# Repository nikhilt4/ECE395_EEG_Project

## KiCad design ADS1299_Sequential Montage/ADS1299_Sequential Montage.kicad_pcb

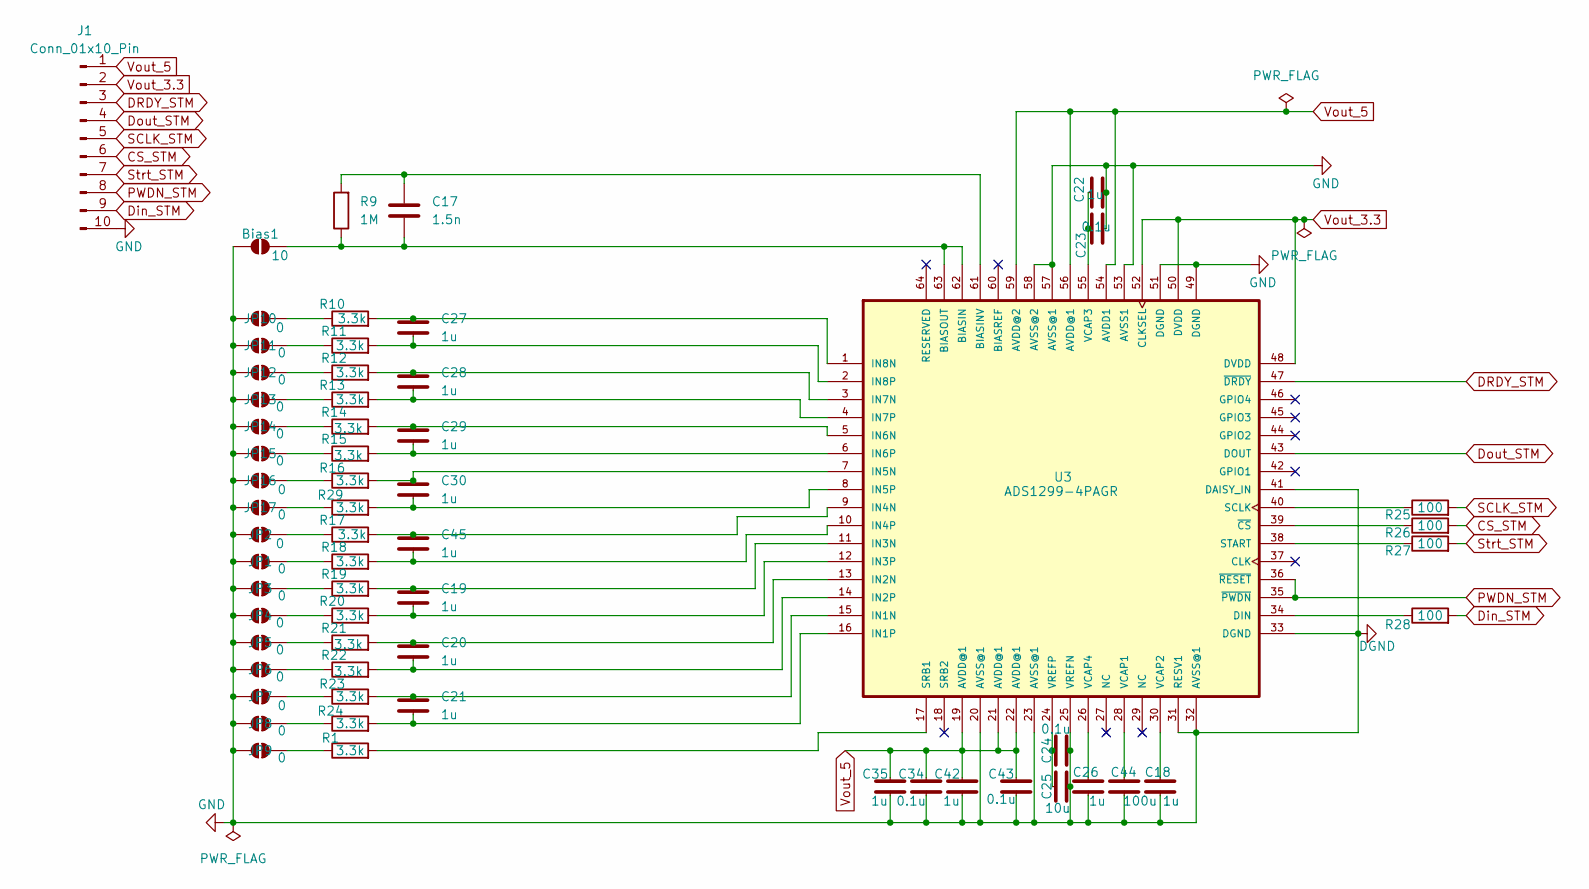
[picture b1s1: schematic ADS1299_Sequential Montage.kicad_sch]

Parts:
Bias1: 10; PinHeader_1x02_P2.54mm_Vertical
C17: 1.5n; C_0805_2012Metric_Pad1.18x1.45mm_HandSolder
C18, C19, C20, C21, C22, C26, C27, C28, C29, C30, C35, C42, C45: 1u; C_0805_2012Metric_Pad1.18x1.45mm_HandSolder
C23, C24, C34, C43: 0.1u; C_0805_2012Metric_Pad1.18x1.45mm_HandSolder
C25: 10u; C_0805_2012Metric_Pad1.18x1.45mm_HandSolder
C44: 100u; C_0805_2012Metric_Pad1.18x1.45mm_HandSolder
J1: Conn_01x10_Pin; PinHeader_1x10_P2.54mm_Vertical
JP1, JP2, JP3, JP4, JP5, JP6, JP7, JP8, JP9, JP10, JP11, JP12, JP13, JP14, JP15, JP16, JP17: 0; PinHeader_1x02_P2.54mm_Vertical
R1, R10, R11, R12, R13, R14, R15, R16, R17, R18, R19, R20, R21, R22, R23, R24, R29: 3.3k; R_0805_2012Metric_Pad1.20x1.40mm_HandSolder
R9: 1M; R_0805_2012Metric_Pad1.20x1.40mm_HandSolder
R25, R26, R27, R28: 100; R_0805_2012Metric_Pad1.20x1.40mm_HandSolder
U3: ADS1299-4PAGR; QFP50P1200X1200X120-64N

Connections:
CS_STM: J1.6, R26.2
DGND: Bias1.1 (A), C18.2, C22.2, C23.2, C24.2, C25.2, C26.2, C34.2, C35.2, C42.2, C43.2, C44.2, J1.10, JP1.1 (A), JP2.1 (A), JP3.1 (A), JP4.1 (A), JP5.1 (A), JP6.1 (A), JP7.1 (A), JP8.1 (A), JP9.1 (A), JP10.1 (A), JP11.1 (A), JP12.1 (A), JP13.1 (A), JP14.1 (A), JP15.1 (A), JP16.1 (A), JP17.1 (A), U3.20 (AVSS@1), U3.23 (AVSS@1), U3.25 (VREFN), U3.31 (RESV1), U3.32 (AVSS@1), U3.33 (DGND), U3.41 (DAISY_IN), U3.49 (DGND), U3.51 (DGND), U3.53 (AVSS1), U3.57 (AVSS@1), U3.58 (AVSS@2)
DRDY_STM: J1.3, U3.47 (~DRDY)
Din_STM: J1.9, R28.2
Dout_STM: J1.4, U3.43 (DOUT)
unnamed: Bias1.2 (B), C17.1, R9.1, U3.62 (BIASIN), U3.63 (BIASOUT)
unnamed: JP1.2 (B), R18.1
unnamed: JP2.2 (B), R17.1
unnamed: JP3.2 (B), R19.1
unnamed: JP4.2 (B), R20.1
unnamed: JP5.2 (B), R21.1
unnamed: JP6.2 (B), R22.1
unnamed: JP7.2 (B), R23.1
unnamed: JP8.2 (B), R24.1
unnamed: JP9.2 (B), R1.1
unnamed: JP10.2 (B), R10.1
unnamed: JP11.2 (B), R11.1
unnamed: JP12.2 (B), R12.1
unnamed: JP13.2 (B), R13.1
unnamed: JP14.2 (B), R14.1
unnamed: JP15.2 (B), R15.1
unnamed: JP16.2 (B), R16.1
unnamed: JP17.2 (B), R29.1
unnamed: C17.2, R9.2, U3.61 (BIASINV)
unnamed: R28.1, U3.34 (DIN)
unnamed: C21.1, R23.2, U3.15 (IN1N)
unnamed: C21.2, R24.2, U3.16 (IN1P)
unnamed: C20.1, R21.2, U3.13 (IN2N)
unnamed: C20.2, R22.2, U3.14 (IN2P)
unnamed: C19.1, R19.2, U3.11 (IN3N)
unnamed: C19.2, R20.2, U3.12 (IN3P)
unnamed: C45.1, R17.2, U3.9 (IN4N)
unnamed: C45.2, R18.2, U3.10 (IN4P)
unnamed: C30.1, R16.2, U3.7 (IN5N)
unnamed: C30.2, R29.2, U3.8 (IN5P)
unnamed: C29.1, R14.2, U3.5 (IN6N)
unnamed: C29.2, R15.2, U3.6 (IN6P)
unnamed: C28.1, R12.2, U3.3 (IN7N)
unnamed: C28.2, R13.2, U3.4 (IN7P)
unnamed: C27.1, R10.2, U3.1 (IN8N)
unnamed: C27.2, R11.2, U3.2 (IN8P)
unnamed: R25.1, U3.40 (SCLK)
unnamed: R1.2, U3.17 (SRB1)
unnamed: R27.1, U3.38 (START)
unnamed: C44.1, U3.28 (VCAP1)
unnamed: C18.1, U3.30 (VCAP2)
unnamed: C22.1, C23.1, U3.55 (VCAP3)
unnamed: C26.1, U3.26 (VCAP4)
unnamed: C24.1, C25.1, U3.24 (VREFP)
unnamed: R26.1, U3.39 (~CS)
PWDN_STM: J1.8, U3.35 (~PWDN), U3.36 (~RESET)
SCLK_STM: J1.5, R25.2
Strt_STM: J1.7, R27.2
Vout_3.3: J1.2, U3.48 (DVDD), U3.50 (DVDD), U3.52 (CLKSEL)
Vout_5: C34.1, C35.1, C42.1, C43.1, J1.1, U3.19 (AVDD@1), U3.21 (AVDD@1), U3.22 (AVDD@1), U3.54 (AVDD1), U3.56 (AVDD@1), U3.59 (AVDD@2)

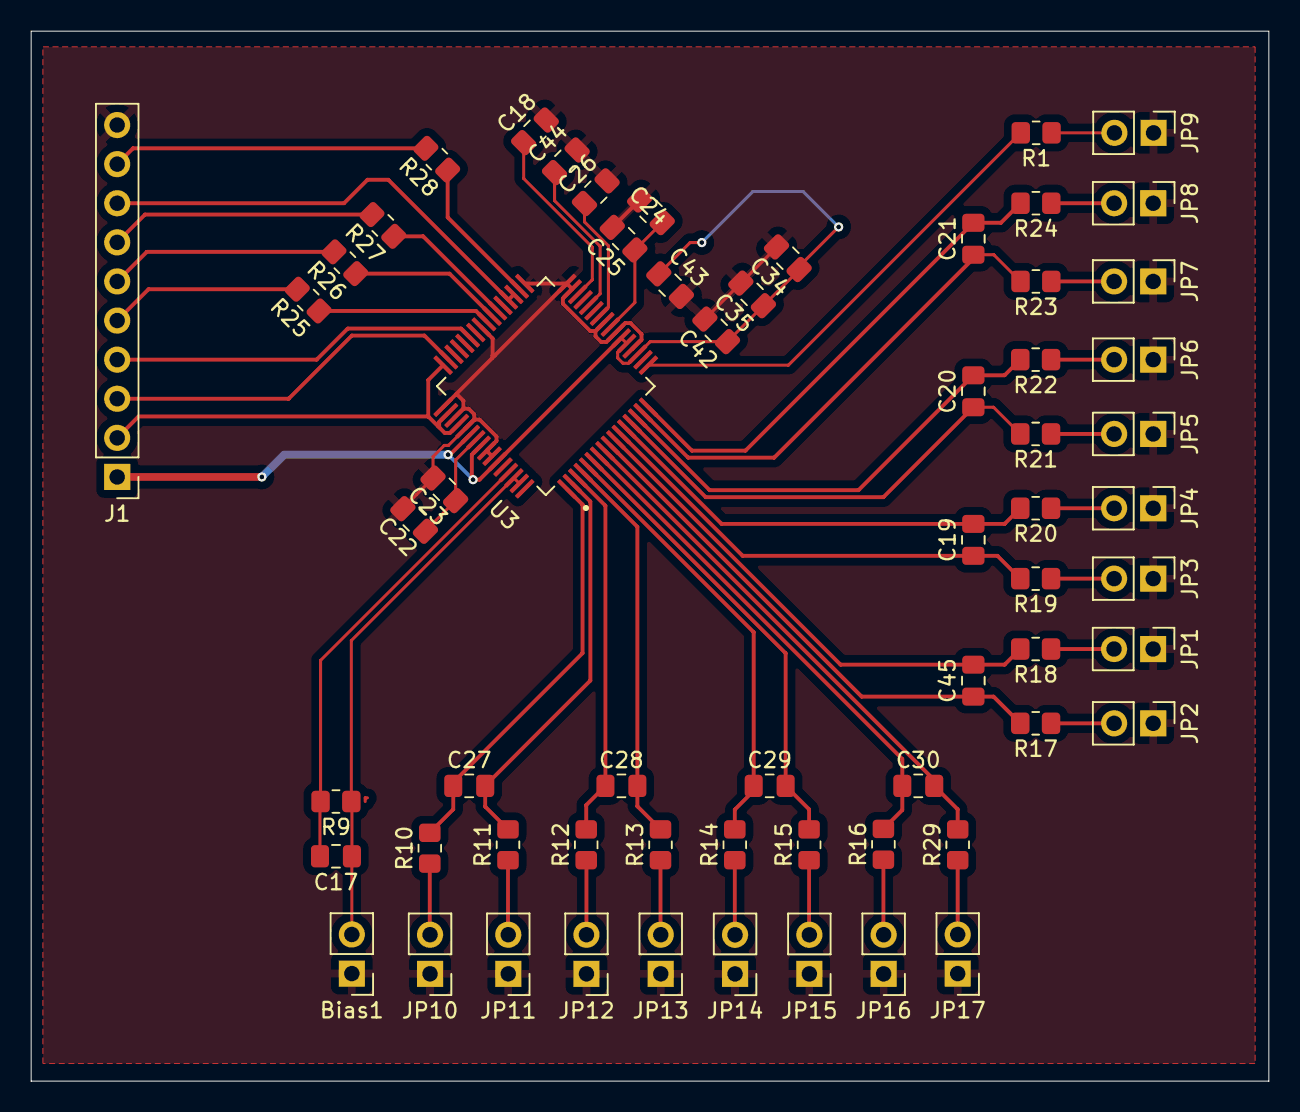
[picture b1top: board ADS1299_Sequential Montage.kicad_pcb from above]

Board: 2 copper layers, 80.4 x 68.2 mm, 62 parts (0 on the bottom side), 55 nets.

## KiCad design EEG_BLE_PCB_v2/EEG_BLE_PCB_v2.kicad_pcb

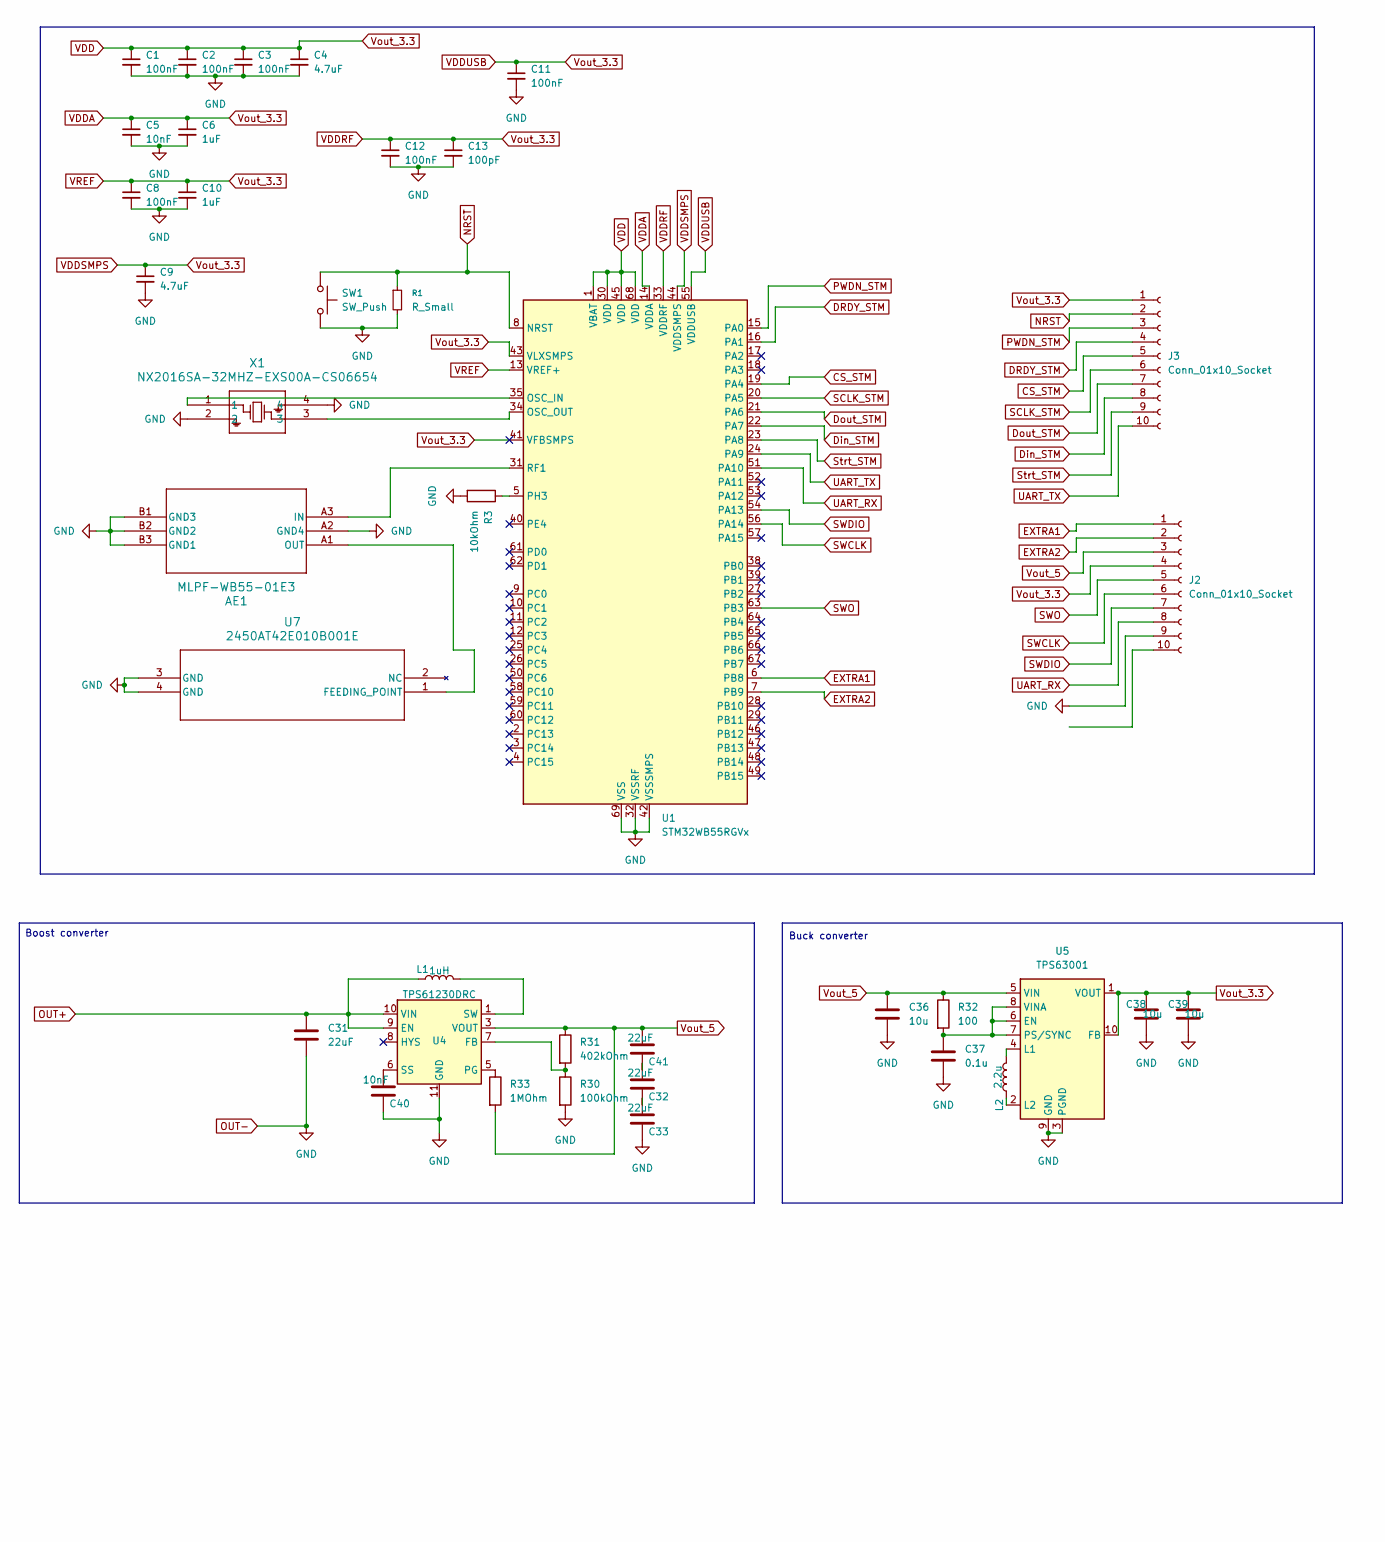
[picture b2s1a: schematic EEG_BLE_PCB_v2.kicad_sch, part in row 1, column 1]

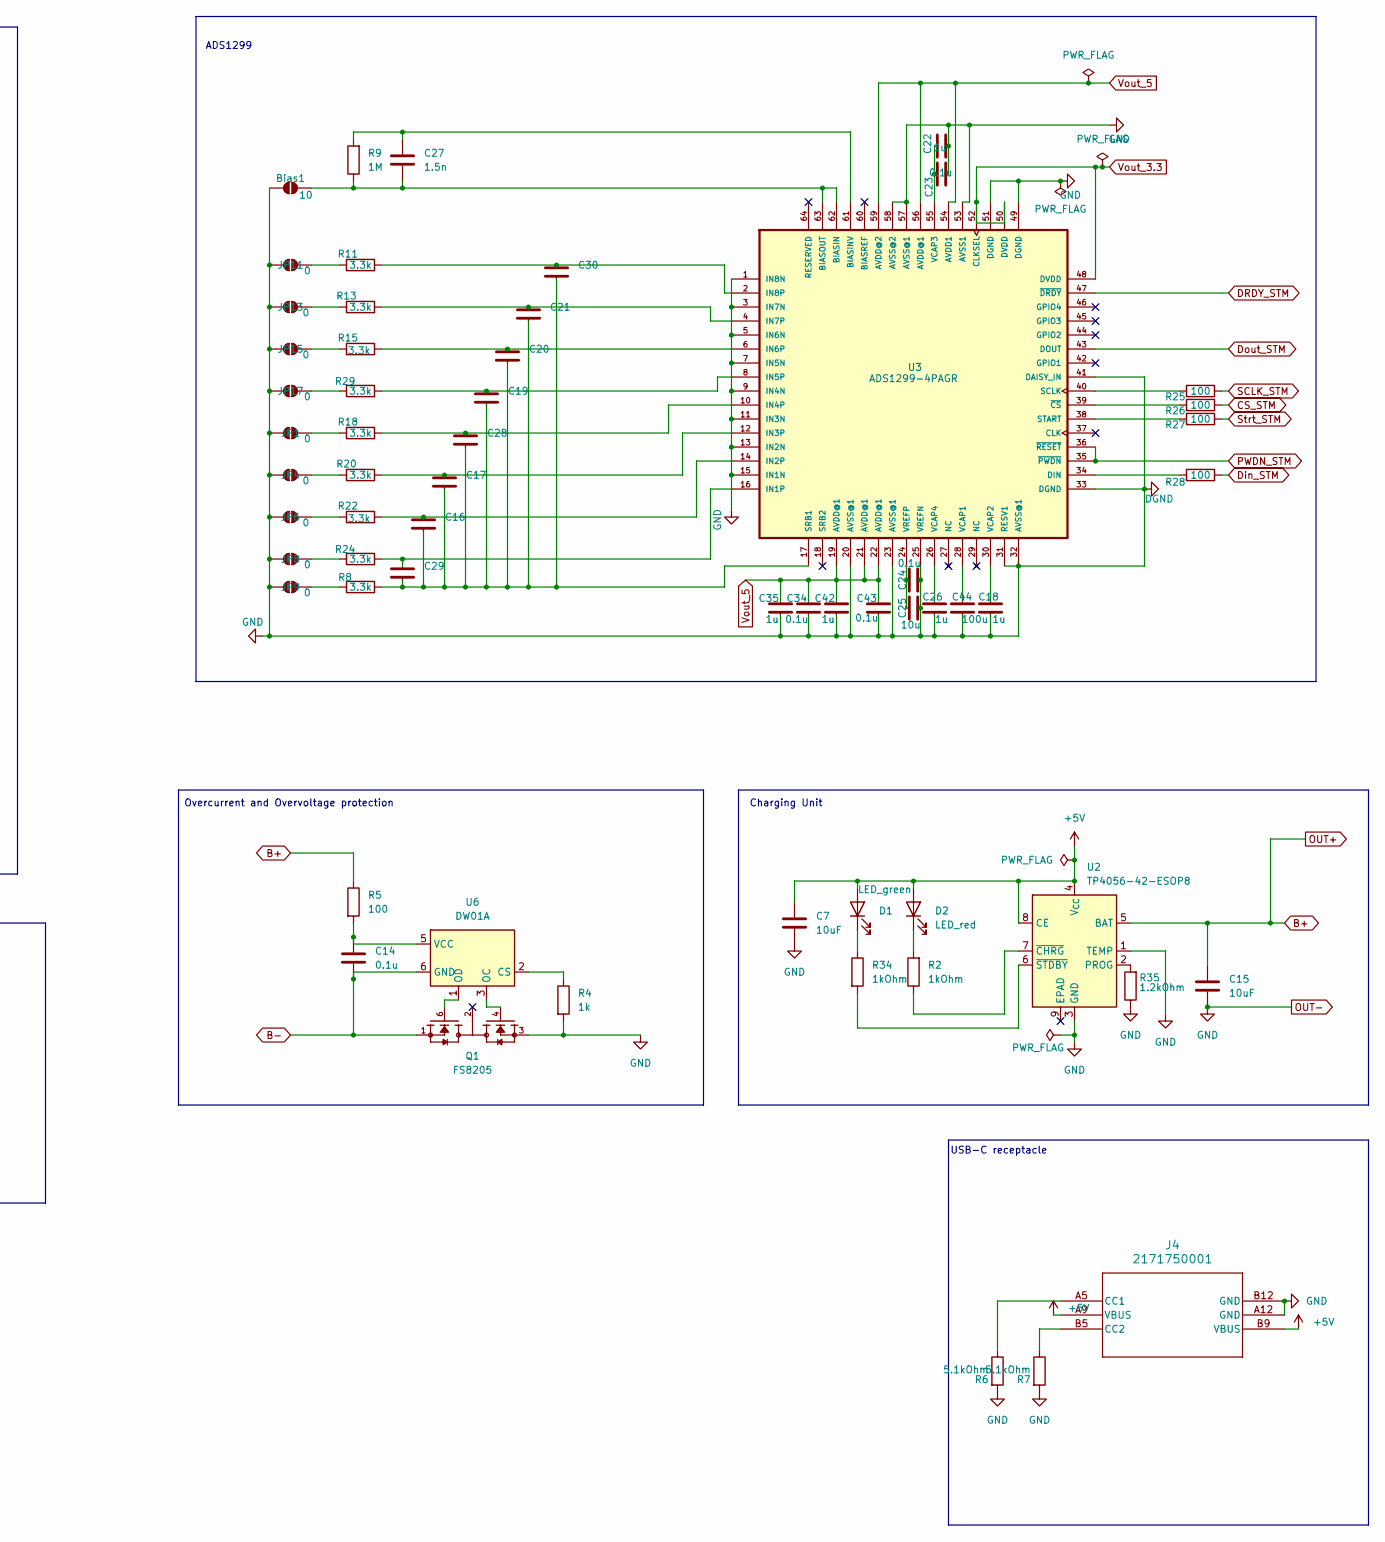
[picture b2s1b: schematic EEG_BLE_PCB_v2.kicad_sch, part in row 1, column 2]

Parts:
AE1: MLPF-WB55-01E3; MLPF-WB55-01E3_STM
Bias1: 10; PinHeader_1x02_P2.54mm_Vertical
C1, C2, C3, C8, C11, C12: 100nF; C_0805_2012Metric_Pad1.18x1.45mm_HandSolder
C4, C9: 4.7uF; C_0805_2012Metric_Pad1.18x1.45mm_HandSolder
C5, C40: 10nF; C_0805_2012Metric_Pad1.18x1.45mm_HandSolder
C6, C10: 1uF; C_0805_2012Metric_Pad1.18x1.45mm_HandSolder
C7, C15: 10uF; C_0805_2012Metric_Pad1.18x1.45mm_HandSolder
C13: 100pF; C_0805_2012Metric_Pad1.18x1.45mm_HandSolder
C14, C23, C24, C34, C37, C43: 0.1u; C_0805_2012Metric_Pad1.18x1.45mm_HandSolder
C16, C17, C19, C20, C21, C28, C29, C30: 100n; C_0805_2012Metric_Pad1.18x1.45mm_HandSolder
C18, C22, C26, C35, C42: 1u; C_0805_2012Metric_Pad1.18x1.45mm_HandSolder
C25, C36, C38, C39: 10u; C_0805_2012Metric_Pad1.18x1.45mm_HandSolder
C27: 1.5n; C_0805_2012Metric_Pad1.18x1.45mm_HandSolder
C31, C32, C33, C41: 22uF; C_0805_2012Metric_Pad1.18x1.45mm_HandSolder
C44: 100u; C_0805_2012Metric_Pad1.18x1.45mm_HandSolder
D1: LED_green; LED_0805_2012Metric_Pad1.15x1.40mm_HandSolder
D2: LED_red; LED_0805_2012Metric_Pad1.15x1.40mm_HandSolder
J2, J3: Conn_01x10_Socket; PinSocket_1x10_P2.54mm_Vertical
J4: 2171750001; 2171750001_MOL
JP1, JP4, JP6, JP8, JP9, JP11, JP13, JP15, JP17: 0; PinHeader_1x02_P2.54mm_Vertical
L1: 1uH; IND_IHLP-1616AB_VIS
L2: 2.2u; IND_VLS3012HBX-2R2M
Q1: FS8205; SOT95P280X145-6N; PARTREV 1.9
R1: R_Small; R_0805_2012Metric_Pad1.20x1.40mm_HandSolder
R2, R34: 1kOhm; R_0805_2012Metric_Pad1.20x1.40mm_HandSolder
R3: 10kOhm; R_0805_2012Metric_Pad1.20x1.40mm_HandSolder
R4: 1k; R_0805_2012Metric_Pad1.20x1.40mm_HandSolder
R5, R25, R26, R27, R28, R32: 100; R_0805_2012Metric_Pad1.20x1.40mm_HandSolder
R6, R7: 5.1kOhm; R_0805_2012Metric_Pad1.20x1.40mm_HandSolder
R8, R11, R13, R15, R18, R20, R22, R24, R29: 3.3k; R_0805_2012Metric_Pad1.20x1.40mm_HandSolder
R9: 1M; R_0805_2012Metric_Pad1.20x1.40mm_HandSolder
R30: 100kOhm; R_0805_2012Metric_Pad1.20x1.40mm_HandSolder
R31: 402kOhm; R_0805_2012Metric_Pad1.20x1.40mm_HandSolder
R33: 1MOhm; R_0805_2012Metric_Pad1.20x1.40mm_HandSolder
R35: 1.2kOhm; R_0805_2012Metric_Pad1.20x1.40mm_HandSolder
SW1: SW_Push; SW_PUSH_6mm
U1: STM32WB55RGVx; QFN-68-1EP_8x8mm_P0.4mm_EP6.4x6.4mm
U2: TP4056-42-ESOP8; SOIC-8-1EP_3.9x4.9mm_P1.27mm_EP2.41x3.3mm_ThermalVias
U3: ADS1299-4PAGR; QFP50P1200X1200X120-64N
U4: TPS61230DRC; Texas_S-PVSON-N10_ThermalVias
U5: TPS63001; Texas_DRC0010J
U6: DW01A; SOT-23-6
U7: 2450AT42E010B001E; 2450AT42E010B_JOT
X1: NX2016SA-32MHZ-EXS00A-CS06654; NX2016SA_NDK

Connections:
+5V: C7.1, D1.2 (A), D2.2 (A), J4.A9 (VBUS), J4.B9 (VBUS), U2.4 (V_{CC}), U2.8 (CE)
B+: C15.1, C31.1, L1.1, R5.1, U2.5 (BAT), U4.9 (EN), U4.10 (VIN)
B-: C14.2, Q1.1, U6.6 (GND)
CS_STM: J3.5, R26.2, U1.19 (PA4)
DRDY_STM: J3.4, U1.16 (PA1), U3.47 (~DRDY)
Din_STM: J3.8, R28.2, U1.22 (PA7)
Dout_STM: J3.7, U1.21 (PA6), U3.43 (DOUT)
EXTRA1: J2.1, U1.6 (PB8)
EXTRA2: J2.2, U1.7 (PB9)
NRST: J3.2, R1.1, SW1.1, U1.8 (NRST)
unnamed: AE1.A3 (IN), U1.31 (RF1)
unnamed: AE1.A1 (OUT), U7.1 (FEEDING_POINT)
unnamed: Bias1.2 (B), C27.1, R9.1, U3.62 (BIASIN), U3.63 (BIASOUT)
unnamed: C32.1, C41.2
unnamed: C32.2, C33.1
unnamed: D1.1 (K), R34.1
unnamed: D2.1 (K), R2.2
unnamed: J4.A5 (CC1), R6.1
unnamed: J4.B5 (CC2), R7.1
unnamed: JP1.2 (B), R18.1
unnamed: JP4.2 (B), R20.1
unnamed: JP6.2 (B), R22.1
unnamed: JP8.2 (B), R24.1
unnamed: JP9.2 (B), R8.1
unnamed: JP11.2 (B), R11.1
unnamed: JP13.2 (B), R13.1
unnamed: JP15.2 (B), R15.1
unnamed: JP17.2 (B), R29.1
unnamed: L1.2, U4.1 (SW), U4.2 (SW)
unnamed: U1.35 (OSC_IN), X1.1
unnamed: U1.34 (OSC_OUT), X1.3
unnamed: R3.1, U1.5 (PH3)
unnamed: R35.2, U2.2 (PROG)
unnamed: R2.1, U2.7 (~CHRG)
unnamed: R34.2, U2.6 (~STDBY)
unnamed: C27.2, R9.2, U3.61 (BIASINV)
unnamed: R28.1, U3.34 (DIN)
unnamed: C29.1, R24.2, U3.16 (IN1P)
unnamed: C16.1, R22.2, U3.14 (IN2P)
unnamed: C17.1, R20.2, U3.12 (IN3P)
unnamed: C28.1, R18.2, U3.10 (IN4P)
unnamed: C19.1, R29.2, U3.8 (IN5P)
unnamed: C20.1, R15.2, U3.6 (IN6P)
unnamed: C21.1, R13.2, U3.4 (IN7P)
unnamed: C30.1, R11.2, U3.2 (IN8P)
unnamed: R25.1, U3.40 (SCLK)
unnamed: C16.2, C17.2, C19.2, C20.2, C21.2, C28.2, C29.2, C30.2, R8.2, U3.17 (SRB1)
unnamed: R27.1, U3.38 (START)
unnamed: C44.1, U3.28 (VCAP1)
unnamed: C18.1, U3.30 (VCAP2)
unnamed: C22.1, C23.1, U3.55 (VCAP3)
unnamed: C26.1, U3.26 (VCAP4)
unnamed: C24.1, C25.1, U3.24 (VREFP)
unnamed: R26.1, U3.39 (~CS)
unnamed: R30.1, R31.2, U4.7 (FB)
unnamed: R33.1, U4.5 (PG)
unnamed: C40.1, U4.6 (SS)
unnamed: C37.1, R32.2, U5.6 (EN), U5.7 (PS/SYNC), U5.8 (VINA)
unnamed: L2.2, U5.4 (L1)
unnamed: L2.1, U5.2 (L2)
unnamed: R4.1, U6.2 (CS)
unnamed: Q1.4, U6.3 (OC)
unnamed: Q1.6, U6.1 (OD)
unnamed: C14.1, R5.2, U6.5 (VCC)
OUT-: AE1.A2 (GND4), AE1.B1 (GND3), AE1.B2 (GND2), AE1.B3 (GND1), Bias1.1 (A), C1.2, C2.2, C3.2, C4.2, C5.2, C6.2, C7.2, C8.2, C9.2, C10.2, C11.2, C12.2, C13.2, C15.2, C18.2, C22.2, C23.2, C24.2, C25.2, C26.2, C31.2, C33.2, C34.2, C35.2, C36.2, C37.2, C38.2, C39.2, C40.2, C42.2, C43.2, C44.2, J2.9, J4.A12 (GND), J4.B12 (GND), JP1.1 (A), JP4.1 (A), JP6.1 (A), JP8.1 (A), JP9.1 (A), JP11.1 (A), JP13.1 (A), JP15.1 (A), JP17.1 (A), Q1.3, R1.2, R3.2, R4.2, R6.2, R7.2, R30.2, R35.1, SW1.2, U1.32 (VSSRF), U1.42 (VSSSMPS), U1.69 (VSS), U2.1 (TEMP), U2.3 (GND), U3.1 (IN8N), U3.3 (IN7N), U3.5 (IN6N), U3.7 (IN5N), U3.9 (IN4N), U3.11 (IN3N), U3.13 (IN2N), U3.15 (IN1N), U3.20 (AVSS@1), U3.23 (AVSS@1), U3.25 (VREFN), U3.31 (RESV1), U3.32 (AVSS@1), U3.33 (DGND), U3.41 (DAISY_IN), U3.49 (DGND), U3.51 (DGND), U3.53 (AVSS1), U3.57 (AVSS@1), U3.58 (AVSS@2), U4.11 (GND), U5.3 (PGND), U5.9 (GND), U5.11 (PGND), U7.3 (GND), U7.4 (GND), X1.2, X1.4
PWDN_STM: J3.3, U1.15 (PA0), U3.35 (~PWDN), U3.36 (~RESET)
SCLK_STM: J3.6, R25.2, U1.20 (PA5)
SWCLK: J2.6, U1.56 (PA14)
SWDIO: J2.7, U1.54 (PA13)
SWO: J2.5, U1.63 (PB3)
Strt_STM: J3.9, R27.2, U1.23 (PA8)
UART_RX: J2.8, U1.51 (PA10)
UART_TX: J3.10, U1.24 (PA9)
VDD: C1.1, C2.1, C3.1, C4.1, C5.1, C6.1, C8.1, C9.1, C10.1, C11.1, C12.1, C13.1, C38.1, C39.1, J2.4, J3.1, U1.1 (VBAT), U1.13 (VREF+), U1.14 (VDDA), U1.30 (VDD), U1.33 (VDDRF), U1.41 (VFBSMPS), U1.43 (VLXSMPS), U1.44 (VDDSMPS), U1.45 (VDD), U1.55 (VDDUSB), U1.68 (VDD), U3.48 (DVDD), U3.50 (DVDD), U3.52 (CLKSEL), U5.1 (VOUT), U5.10 (FB)
Vout_5: C34.1, C35.1, C36.1, C41.1, C42.1, C43.1, J2.3, R31.1, R32.1, R33.2, U3.19 (AVDD@1), U3.21 (AVDD@1), U3.22 (AVDD@1), U3.54 (AVDD1), U3.56 (AVDD@1), U3.59 (AVDD@2), U4.3 (VOUT), U4.4 (VOUT), U5.5 (VIN)

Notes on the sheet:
ADS1299
Boost converter
Charging Unit
USB-C receptacle
Buck converter
Overcurrent and Overvoltage protection

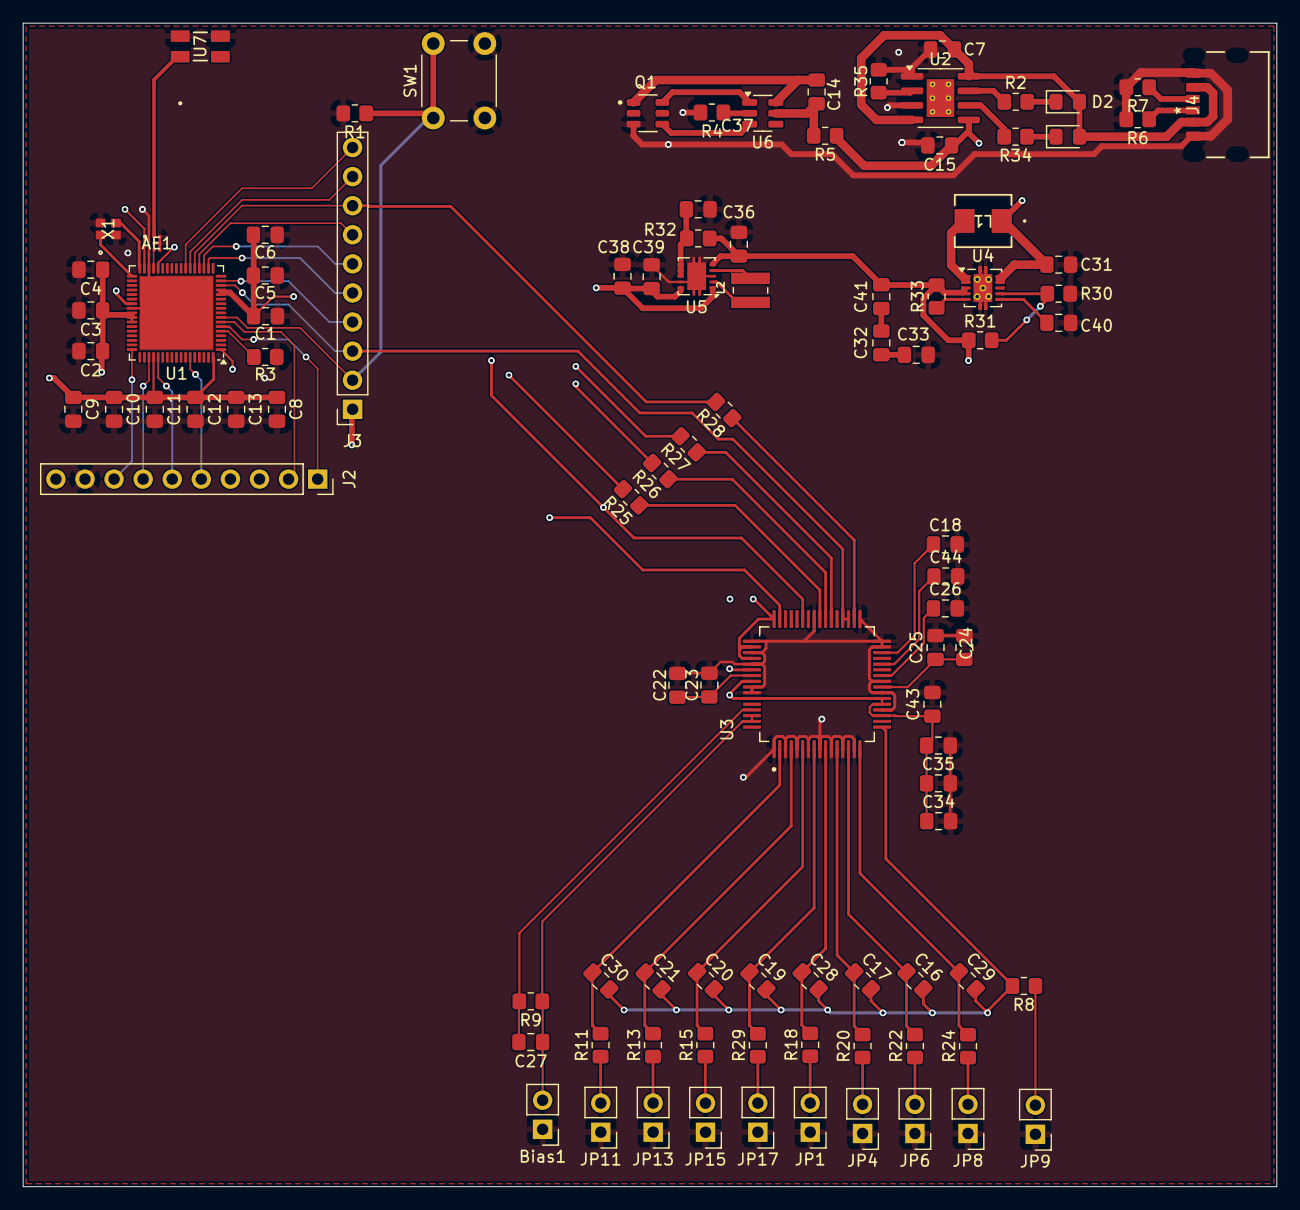
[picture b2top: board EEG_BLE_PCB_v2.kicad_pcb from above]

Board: 4 copper layers, 109.5 x 101.6 mm, 99 parts (0 on the bottom side), 75 nets.

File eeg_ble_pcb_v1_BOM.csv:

Reference,Qty,Value,DNP,Exclude from BOM,Exclude from Board,Footprint,Source,Part No.,Digikey Part No.,,,,Datasheet
AE1,1,MLPF-WB55-01E3,,,,395_eeg_footprint_library:MLPF-WB55-01E3_STM,,,,,,,https://www.st.com/resource/en/datasheet/mlpf-wb55-01e3.pdf
Bias1,1,10,,Excluded from BOM,,Connector_PinHeader_2.54mm:PinHeader_1x02_P2.54mm_Vertical,,,,,,,~
"C1,C2,C3,C8,C11,C12",6,100nF,,,,Capacitor_SMD:C_0805_2012Metric_Pad1.18x1.45mm_HandSolder,,,,,,,~
"C4,C9",2,4.7uF,,,,Capacitor_SMD:C_0805_2012Metric_Pad1.18x1.45mm_HandSolder,,,,,,,~
"C5,C40",2,10nF,,,,Capacitor_SMD:C_0805_2012Metric_Pad1.18x1.45mm_HandSolder,,,,,,,~
"C6,C10",2,1uF,,,,Capacitor_SMD:C_0805_2012Metric_Pad1.18x1.45mm_HandSolder,,,,,,,~
"C7,C15",2,10uF,,,,Capacitor_SMD:C_0805_2012Metric_Pad1.18x1.45mm_HandSolder,,,,,,,~
C13,1,100pF,,,,Capacitor_SMD:C_0805_2012Metric_Pad1.18x1.45mm_HandSolder,,,,,,,~
"C14,C23,C24,C34,C37,C43",6,0.1u,,,,Capacitor_SMD:C_0805_2012Metric_Pad1.18x1.45mm_HandSolder,,,,,,,~
C17,1,1n,,,,Capacitor_SMD:C_0805_2012Metric_Pad1.18x1.45mm_HandSolder,,,,,,,~
"C18,C19,C20,C21,C22,C26,C27,C28,C29,C30,C35,C42,C45",13,1u,,,,Capacitor_SMD:C_0805_2012Metric_Pad1.18x1.45mm_HandSolder,,,,,,,~
"C25,C36,C38,C39",4,10u,,,,Capacitor_SMD:C_0805_2012Metric_Pad1.18x1.45mm_HandSolder,,,,,,,~
"C31,C32,C33,C41",4,22uF,,,,Capacitor_SMD:C_0805_2012Metric_Pad1.18x1.45mm_HandSolder,,,,,,,~
C44,1,100u,,,,Capacitor_SMD:C_0805_2012Metric_Pad1.18x1.45mm_HandSolder,,,,,,,~
D1,1,LED_green,,,,LED_SMD:LED_0805_2012Metric_Pad1.15x1.40mm_HandSolder,,,,,,,~
D2,1,LED_red,,,,LED_SMD:LED_0805_2012Metric_Pad1.15x1.40mm_HandSolder,,,,,,,~
"J2,J3",2,Conn_01x10_Socket,,,,Connector_PinSocket_2.54mm:PinSocket_1x10_P2.54mm_Vertical,,,,,,,~
J4,1,2171750001,,,,395_eeg_footprint_library:2171750001_MOL,,,,,,,https://www.molex.com/en-us/products/part-detail-pdf/2171750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
"JP1,JP2,JP3,JP4,JP5,JP6,JP7,JP8,JP10,JP11,JP12,JP13,JP14,JP15,JP16,JP17",16,0,,Excluded from BOM,,Connector_PinHeader_2.54mm:PinHeader_1x02_P2.54mm_Vertical,,,,,,,~
L1,1,1uH,,,,395_eeg_footprint_library:IND_IHLP-1616AB_VIS,,,,,,,~
L2,1,2.2u,,,,395_eeg_footprint_library:IND_VLS3012HBX-2R2M,,,,,,,~
Q1,1,FS8205,,,,395_eeg_footprint_library:SOT95P280X145-6N,,,,,,,
R1,1,R_Small,,,,Resistor_SMD:R_0805_2012Metric_Pad1.20x1.40mm_HandSolder,,,,,,,~
"R2,R34",2,1kOhm,,,,Resistor_SMD:R_0805_2012Metric_Pad1.20x1.40mm_HandSolder,,,,,,,~
R3,1,10kOhm,,,,Resistor_SMD:R_0805_2012Metric_Pad1.20x1.40mm_HandSolder,,,,,,,~
R4,1,1k,,,,Resistor_SMD:R_0805_2012Metric_Pad1.20x1.40mm_HandSolder,,,,,,,~
"R5,R25,R26,R27,R28,R32",6,100,,,,Resistor_SMD:R_0805_2012Metric_Pad1.20x1.40mm_HandSolder,,,,,,,~
"R6,R7",2,5.1kOhm,,,,Resistor_SMD:R_0805_2012Metric_Pad1.20x1.40mm_HandSolder,,,,,,,~
R9,1,1M,,,,Resistor_SMD:R_0805_2012Metric_Pad1.20x1.40mm_HandSolder,,,,,,,~
"R10,R11,R12,R13,R14,R15,R16,R17,R18,R19,R20,R21,R22,R23,R24,R29",16,3.3k,,,,Resistor_SMD:R_0805_2012Metric_Pad1.20x1.40mm_HandSolder,,,,,,,~
R30,1,100kOhm,,,,Resistor_SMD:R_0805_2012Metric_Pad1.20x1.40mm_HandSolder,,,,,,,~
R31,1,402kOhm,,,,Resistor_SMD:R_0805_2012Metric_Pad1.20x1.40mm_HandSolder,,,,,,,~
R33,1,1MOhm,,,,Resistor_SMD:R_0805_2012Metric_Pad1.20x1.40mm_HandSolder,,,,,,,~
R35,1,1.2kOhm,,,,Resistor_SMD:R_0805_2012Metric_Pad1.20x1.40mm_HandSolder,,,,,,,~
SW1,1,SW_Push,,,,Button_Switch_THT:SW_PUSH_6mm,,,,,,,~
U1,1,STM32WB55RGVx,,,,Package_DFN_QFN:QFN-68-1EP_8x8mm_P0.4mm_EP6.4x6.4mm,,,,,,,https://www.st.com/resource/en/datasheet/stm32wb55rg.pdf
U2,1,TP4056-42-ESOP8,,,,Package_SO:SOIC-8-1EP_3.9x4.9mm_P1.27mm_EP2.41x3.3mm_ThermalVias,,,,,,,https://www.lcsc.com/datasheet/lcsc_datasheet_2410121619_TOP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
U3,1,ADS1299-4PAGR,,,,395_eeg_footprint_library:QFP50P1200X1200X120-64N,,,,,,,
U4,1,TPS61230DRC,,,,Package_SON:Texas_S-PVSON-N10_ThermalVias,,,,,,,http://www.ti.com/lit/ds/symlink/tps61232.pdf
U5,1,TPS63001,,,,Package_SON:Texas_DRC0010J,,,,,,,http://www.ti.com/lit/ds/symlink/tps63000.pdf
U6,1,DW01A,,,,Package_TO_SOT_SMD:SOT-23-6,,,,,,,https://hmsemi.com/downfile/DW01A.PDF
U7,1,2450AT42E010B001E,,,,395_eeg_footprint_library:2450AT42E010B_JOT,,,,,,,2450AT42E010B001E
X1,1,NX2016SA-32MHZ-EXS00A-CS06654,,,,395_eeg_footprint_library:NX2016SA_NDK,,,,,,,NX2016SA-32MHZ-EXS00A-CS06654

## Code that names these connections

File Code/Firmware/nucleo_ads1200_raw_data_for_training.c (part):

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
static inline void ADS_CS_LOW(void)
{
    HAL_GPIO_WritePin(CS_STM_GPIO_Port, CS_STM_Pin, GPIO_PIN_RESET);
}

static inline void ADS_CS_HIGH(void)
{
    HAL_GPIO_WritePin(CS_STM_GPIO_Port, CS_STM_Pin, GPIO_PIN_SET);
}

static void ADS_SmallDelay(void)
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
static void ADS_GPIO_InitPins(void)
{
    HAL_GPIO_WritePin(CS_STM_GPIO_Port, CS_STM_Pin, GPIO_PIN_SET);         // CS idle high
    HAL_GPIO_WritePin(PWDN_STM_GPIO_Port, PWDN_STM_Pin, GPIO_PIN_SET);     // not in power-down
    HAL_GPIO_WritePin(START_STM_GPIO_Port, START_STM_Pin, GPIO_PIN_RESET); // START low initially
}

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    HAL_Delay(10);

    /* Hardware reset through PWDN */
    HAL_GPIO_WritePin(PWDN_STM_GPIO_Port, PWDN_STM_Pin, GPIO_PIN_RESET);
    HAL_Delay(10);
    HAL_GPIO_WritePin(PWDN_STM_GPIO_Port, PWDN_STM_Pin, GPIO_PIN_SET);
    HAL_Delay(50);

    /* Software reset */
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  HAL_GPIO_WritePin(START_STM_GPIO_Port, START_STM_Pin, GPIO_PIN_RESET);

  /*Configure GPIO pin Output Level */
  HAL_GPIO_WritePin(GPIOA, PWDN_STM_Pin|CS_STM_Pin, GPIO_PIN_SET);

  /*Configure GPIO pins : START_STM_Pin PWDN_STM_Pin CS_STM_Pin */
  GPIO_InitStruct.Pin = START_STM_Pin|PWDN_STM_Pin|CS_STM_Pin;
  GPIO_InitStruct.Mode = GPIO_MODE_OUTPUT_PP;
  GPIO_InitStruct.Pull = GPIO_NOPULL;
  GPIO_InitStruct.Speed = GPIO_SPEED_FREQ_LOW;
  HAL_GPIO_Init(GPIOA, &GPIO_InitStruct);

  /*Configure GPIO pin : DRDY_STM_Pin */
  GPIO_InitStruct.Pin = DRDY_STM_Pin;
  GPIO_InitStruct.Mode = GPIO_MODE_IT_FALLING;
  GPIO_InitStruct.Pull = GPIO_NOPULL;
  HAL_GPIO_Init(DRDY_STM_GPIO_Port, &GPIO_InitStruct);

  /*Configure GPIO pins : USB_DM_Pin USB_DP_Pin */
  GPIO_InitStruct.Pin = USB_DM_Pin|USB_DP_Pin;
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/* USER CODE BEGIN 4 */
void HAL_GPIO_EXTI_Callback(uint16_t GPIO_Pin)
{
    if (GPIO_Pin == DRDY_STM_Pin)
    {
        drdy_count++;
    }
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
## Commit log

2026-02-24 Initial KiCad project commit
2026-02-24 Track KiCad symbol library table
2026-02-24 Decoupling capacitors and NRST
2026-02-24 Added oscillator
2026-02-26 Addded BMS
2026-02-26 BMS and footprint sync
2026-02-28 ADC, Buck, Boost, and charging unit added
2026-03-01 PCB ADS1299 and jumper connections
2026-03-02 nothing
2026-03-02 error check
2026-03-03 errors fixed
2026-03-03 weird change
2026-03-03 Schematics, PCB, and BOM done
2026-03-03 updated BOM csv
2026-03-03 small pcb change
2026-03-04 PCB ADS1299 and Charging done
2026-03-06 stm connections v1
2026-03-06 PCB moved around
2026-03-10 Input Cap change and PCB connections
2026-03-25 Full Differential PCB done
2026-03-31 PCB v1 modified for RF
2026-03-31 PCB v2, ADS ref and seq montage included
2026-04-07 added all code and firmware
2026-04-07 added stm firmware
2026-04-10 new code and scripts
2026-04-10 firmware change
2026-04-17 display eeg changes
2026-05-12 major code script edits and final versions after demo

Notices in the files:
Code/Firmware/nucleo_ads1200_raw_data_for_training.c:
Copyright (c) 2026 STMicroelectronics.
All rights reserved.
This software is licensed under terms that can be found in the LICENSE file
